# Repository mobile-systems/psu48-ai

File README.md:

# PSU48-800 — БП 220 В AC → 48 В DC, 800 Вт

Проект импульсного блока питания (PFC + LLC), разрабатывается в KiCad 10.

- `JOURNAL.md` — инженерный журнал (этапы, решения, изменения).
- `docs/SPEC.md` — техническое задание.
- `docs/DESIGN.md` — расчёт топологии.
- `kicad/` — проект KiCad (схема, плата, библиотеки).
- `tools/` — скрипты генерации и проверки (Python, bundled с KiCad).
- `production/` — производственные файлы (Gerber, drill, BOM, CPL, PDF).

Сборка проекта (генерация схемы/платы) и выпуск — см. журнал, этапы работ.

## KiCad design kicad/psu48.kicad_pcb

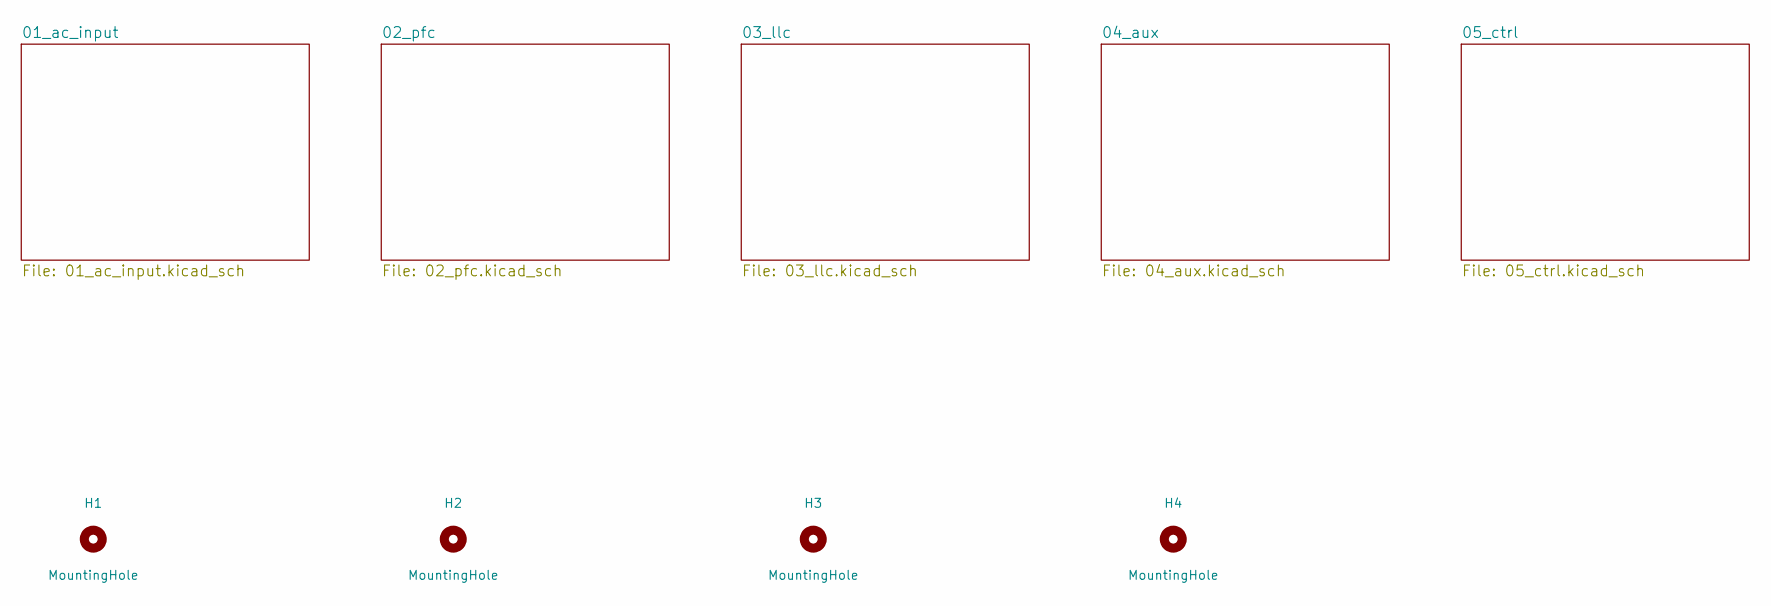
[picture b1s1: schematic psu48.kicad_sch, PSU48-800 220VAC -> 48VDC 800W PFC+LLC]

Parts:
H1, H2, H3, H4: MountingHole; MountingHole_3.2mm_M3

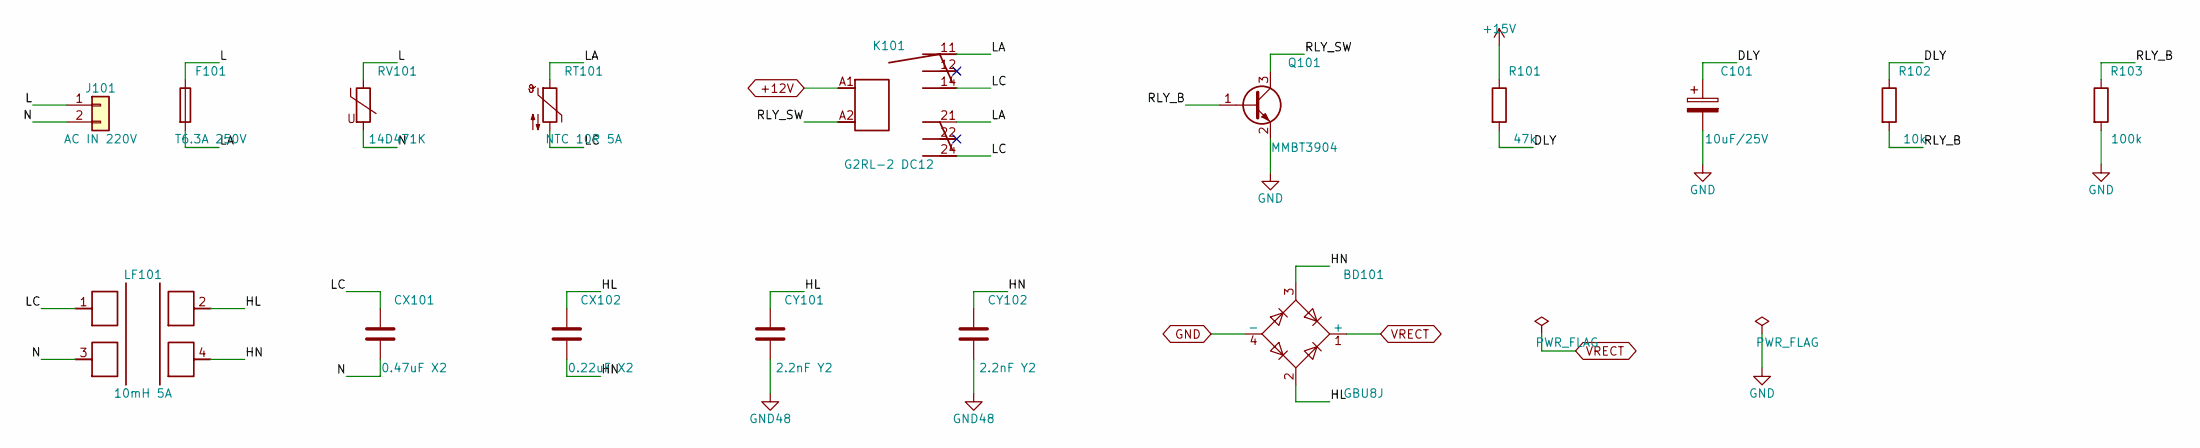
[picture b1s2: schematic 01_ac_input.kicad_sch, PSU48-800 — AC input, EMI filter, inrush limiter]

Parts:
BD101: GBU8J; Diode_Bridge_Vishay_GBU
C101: 10uF/25V; CP_Radial_D5.0mm_P2.50mm
CX101: 0.47uF X2; C_Rect_L27.0mm_W11.0mm_P22.00mm
CX102: 0.22uF X2; C_Rect_L16.5mm_W5.0mm_P15.00mm_MKT
CY101, CY102: 2.2nF Y2; C_Disc_D10.5mm_W5.0mm_P7.50mm
F101: T6.3A 250V; Fuseholder_Clip-5x20mm_Littelfuse_111_Inline_P20.00x5.00mm_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
J101: AC IN 220V; TerminalBlock_MaiXu_MX126-5.0-02P_1x02_P5.00mm
K101: G2RL-2 DC12; Relay_DPDT_Omron_G2RL-2
LF101: 10mH 5A; CMChoke_25x20_P20x10
Q101: MMBT3904; SOT-23
R101: 47k; R_0805_2012Metric
R102: 10k; R_0805_2012Metric
R103: 100k; R_0805_2012Metric
RT101: NTC 10R 5A; NTC_D11.0mm_P5.00mm
RV101: 14D471K; RV_Disc_D15.5mm_W5.9mm_P7.5mm

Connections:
01_ac_input/DLY: C101.1, R101.2, R102.1
01_ac_input/HL: BD101.2, CX102.1, CY101.1, LF101.2
01_ac_input/HN: BD101.3, CX102.2, CY102.1, LF101.4
01_ac_input/L: F101.1, J101.1, RV101.1
01_ac_input/LA: F101.2, K101.11, K101.21, RT101.1
01_ac_input/LC: CX101.1, K101.14, K101.24, LF101.1, RT101.2
01_ac_input/N: CX101.2, J101.2, LF101.3, RV101.2
01_ac_input/RLY_B: Q101.1 (B), R102.2, R103.1
01_ac_input/RLY_SW: K101.A2, Q101.3 (C)
+12V: K101.A1; also elsewhere on the board
+15V: R101.1; also elsewhere on the board
GND: BD101.4 (-), C101.2, Q101.2 (E), R103.2; also elsewhere on the board
GND48: CY101.2, CY102.2; also elsewhere on the board
VRECT: BD101.1 (+); also elsewhere on the board

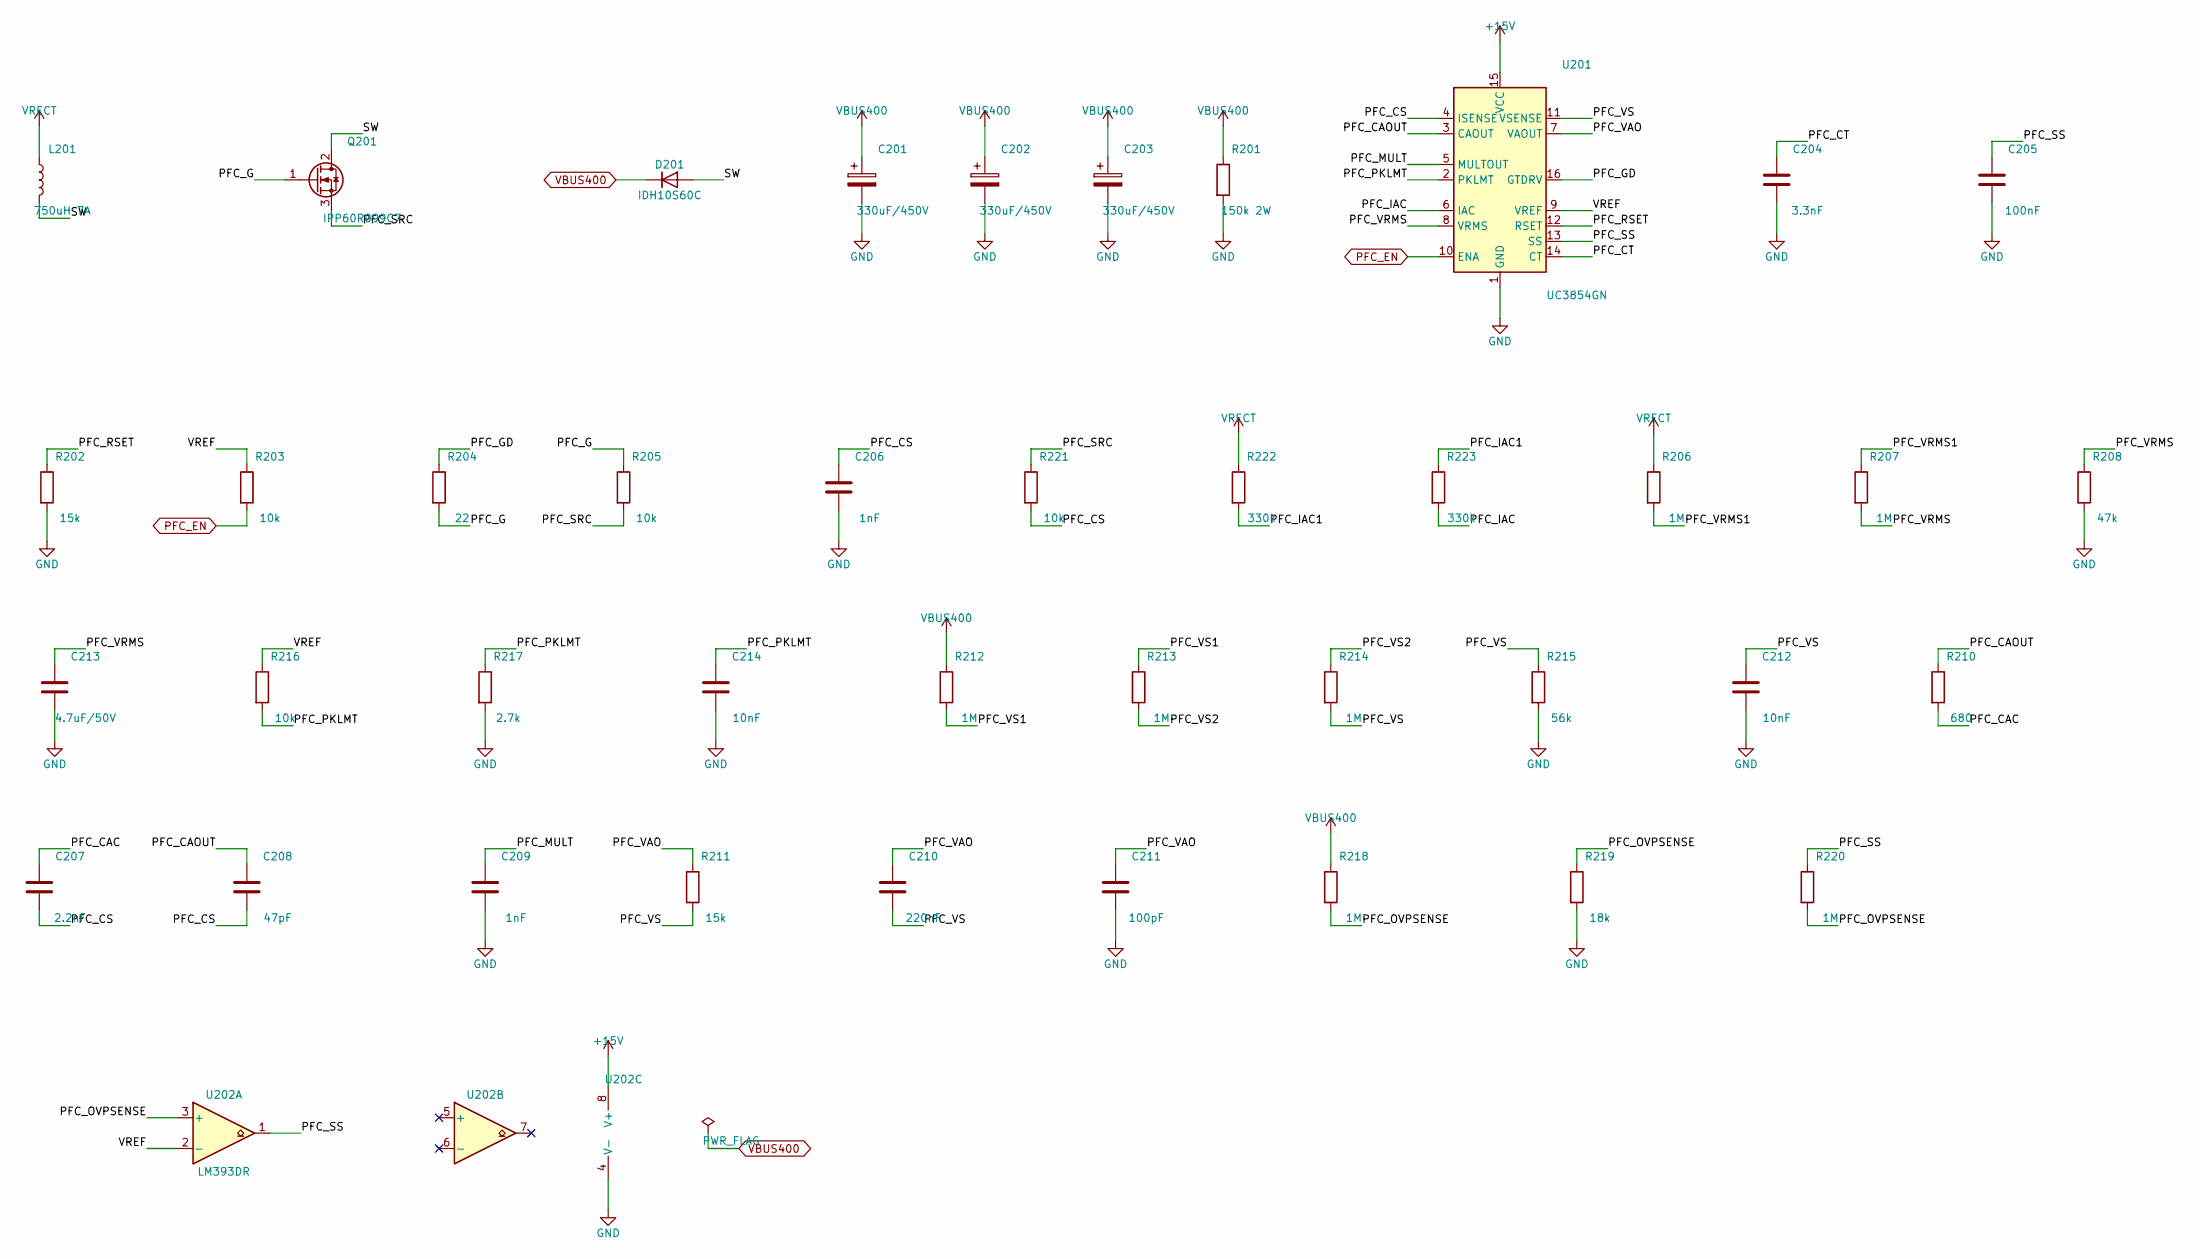
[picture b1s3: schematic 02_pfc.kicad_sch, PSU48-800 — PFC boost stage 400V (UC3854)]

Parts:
C201, C202, C203: 330uF/450V; CP_Radial_D35.0mm_P10.00mm
C204: 3.3nF; C_0805_2012Metric
C205: 100nF; C_0805_2012Metric
C206, C209: 1nF; C_0805_2012Metric
C207: 2.2nF; C_0805_2012Metric
C208: 47pF; C_0805_2012Metric
C210: 220nF; C_0805_2012Metric
C211: 100pF; C_0805_2012Metric
C212, C214: 10nF; C_0805_2012Metric
C213: 4.7uF/50V; C_1210_3225Metric
D201: IDH10S60C; TO-220-3_Vertical
L201: 750uH 7A; L_THT_D30.0mm_P15.00mm
Q201: IPP60R099C7; TO-220-3_Vertical
R201: 150k 2W; R_Axial_DIN0617_L17.0mm_D6.0mm_P25.40mm_Horizontal
R202, R211: 15k; R_0805_2012Metric
R203, R205, R216, R221: 10k; R_0805_2012Metric
R204: 22; R_0805_2012Metric
R206, R207, R212, R213, R214, R218: 1M; R_1206_3216Metric
R208: 47k; R_0805_2012Metric
R210: 680; R_0805_2012Metric
R215: 56k; R_0805_2012Metric
R217: 2.7k; R_0805_2012Metric
R219: 18k; R_0805_2012Metric
R220: 1M; R_0805_2012Metric
R222, R223: 330k; R_1206_3216Metric
U201: UC3854GN; DIP-16_W7.62mm
U202: LM393DR; SOIC-8_3.9x4.9mm_P1.27mm

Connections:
02_pfc/PFC_CAC: C207.1, R210.2
02_pfc/PFC_CAOUT: C208.1, R210.1, U201.3 (CAOUT)
02_pfc/PFC_CS: C206.1, C207.2, C208.2, R221.2, U201.4 (ISENSE)
02_pfc/PFC_CT: C204.1, U201.14 (CT)
02_pfc/PFC_G: Q201.1 (G), R204.2, R205.1
02_pfc/PFC_GD: R204.1, U201.16 (GTDRV)
02_pfc/PFC_IAC: R223.2, U201.6 (IAC)
02_pfc/PFC_IAC1: R222.2, R223.1
02_pfc/PFC_MULT: C209.1, U201.5 (MULTOUT)
02_pfc/PFC_OVPSENSE: R218.2, R219.1, R220.2, U202.3 (+)
02_pfc/PFC_PKLMT: C214.1, R216.2, R217.1, U201.2 (PKLMT)
02_pfc/PFC_RSET: R202.1, U201.12 (RSET)
02_pfc/PFC_SRC: Q201.3 (S), R205.2, R221.1
02_pfc/PFC_SS: C205.1, R220.1, U201.13 (SS), U202.1
02_pfc/PFC_VAO: C210.1, C211.1, R211.1, U201.7 (VAOUT)
02_pfc/PFC_VRMS: C213.1, R207.2, R208.1, U201.8 (VRMS)
02_pfc/PFC_VRMS1: R206.2, R207.1
02_pfc/PFC_VS: C210.2, C212.1, R211.2, R214.2, R215.1, U201.11 (VSENSE)
02_pfc/PFC_VS1: R212.2, R213.1
02_pfc/PFC_VS2: R213.2, R214.1
02_pfc/SW: D201.2 (A), L201.2, Q201.2 (D)
02_pfc/VREF: R203.1, R216.1, U201.9 (VREF), U202.2 (-)
+15V: U201.15 (VCC), U202.8 (V+); also elsewhere on the board
GND: C201.2, C202.2, C203.2, C204.2, C205.2, C206.2, C209.2, C211.2, C212.2, C213.2, C214.2, R201.2, R202.2, R208.2, R215.2, R217.2, R219.2, U201.1 (GND), U202.4 (V-); also elsewhere on the board
PFC_EN: R203.2, U201.10 (ENA); also elsewhere on the board
VBUS400: C201.1, C202.1, C203.1, D201.1 (K), R201.1, R212.1, R218.1; also elsewhere on the board
VRECT: L201.1, R206.1, R222.1; also elsewhere on the board

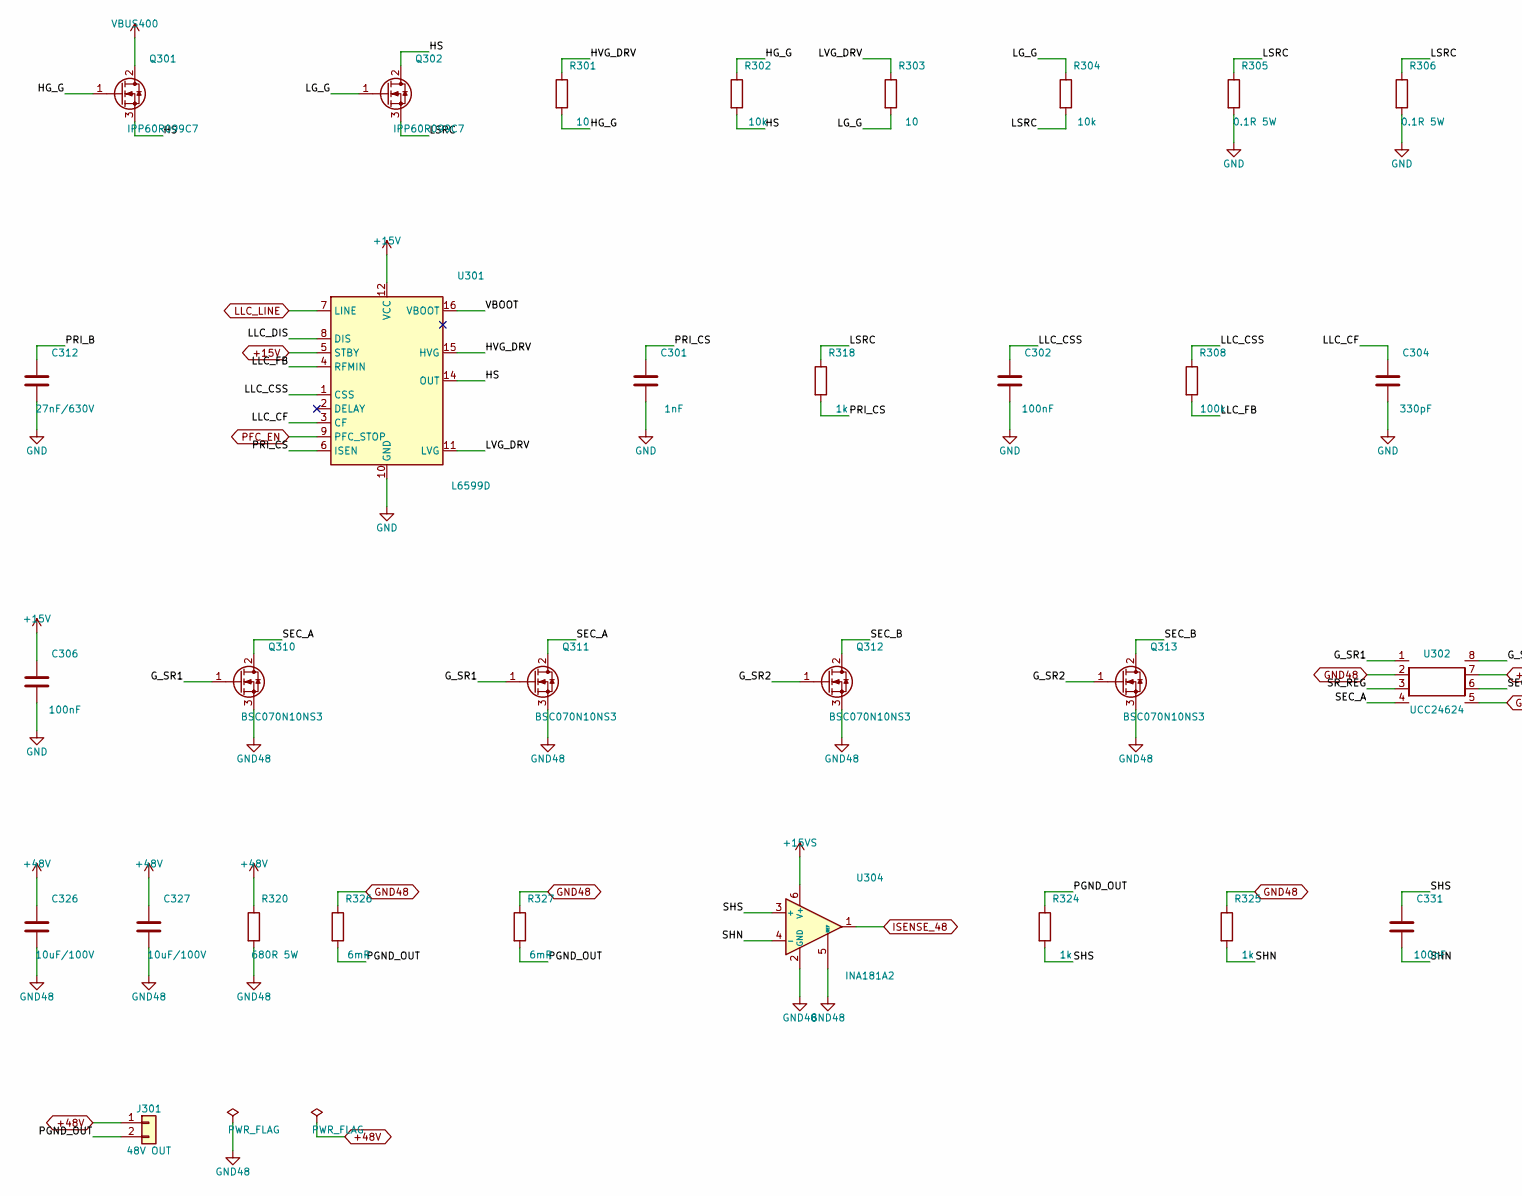
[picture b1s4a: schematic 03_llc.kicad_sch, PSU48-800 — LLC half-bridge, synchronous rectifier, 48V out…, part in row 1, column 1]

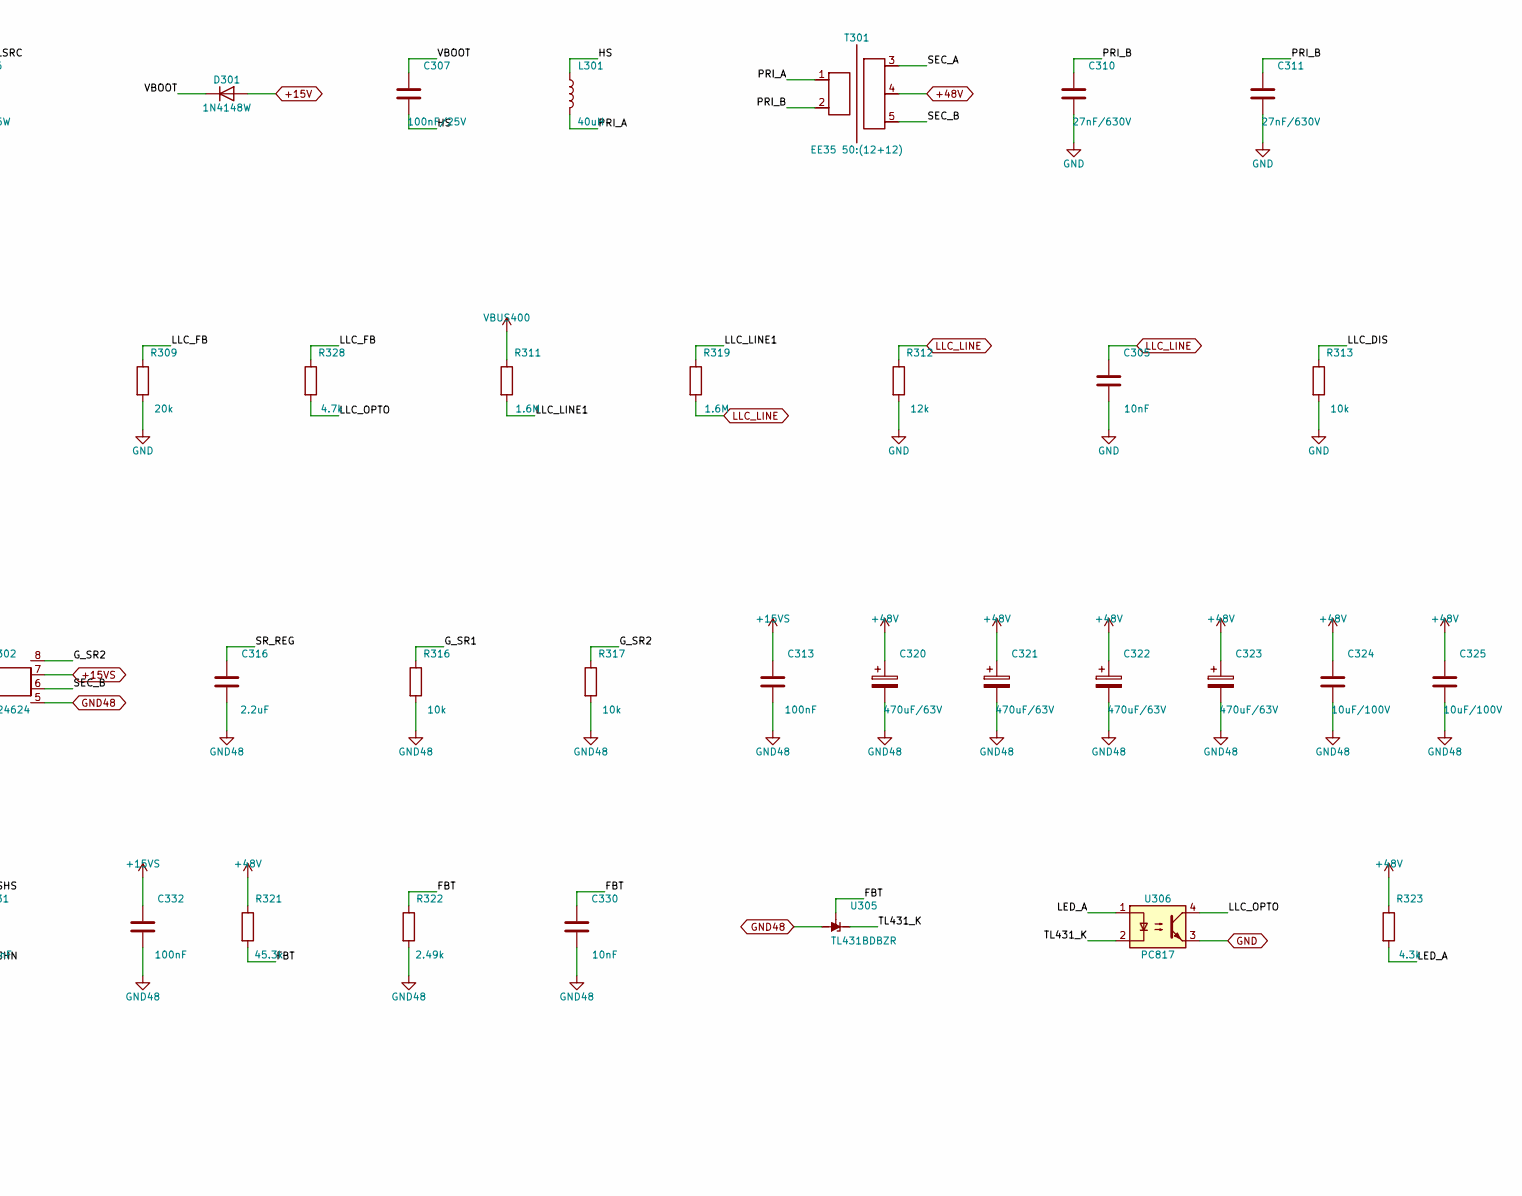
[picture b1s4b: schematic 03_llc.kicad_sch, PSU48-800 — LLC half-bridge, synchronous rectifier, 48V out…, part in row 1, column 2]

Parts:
C301: 1nF; C_0805_2012Metric
C302, C306, C313, C331, C332: 100nF; C_0805_2012Metric
C304: 330pF; C_0805_2012Metric
C305, C330: 10nF; C_0805_2012Metric
C307: 100nF/25V; C_0805_2012Metric
C310, C311, C312: 27nF/630V; C_Rect_L16.5mm_W5.0mm_P15.00mm_MKT
C316: 2.2uF; C_0805_2012Metric
C320, C321, C322, C323: 470uF/63V; CP_Radial_D16.0mm_P7.50mm
C324, C325, C326, C327: 10uF/100V; C_1210_3225Metric
D301: 1N4148W; D_SOD-123
J301: 48V OUT; PinHeader_1x02_P2.54mm_Vertical
L301: 40uH; L_THT_25x20_P10.00mm
Q301, Q302: IPP60R099C7; TO-247-3_Vertical
Q310, Q311, Q312, Q313: BSC070N10NS3; PQFN-8-EP_6x5mm_P1.27mm_Generic
R301, R303: 10; R_0805_2012Metric
R302, R304, R313, R316, R317: 10k; R_0805_2012Metric
R305, R306: 0.1R 5W; R_Axial_DIN0617_L17.0mm_D6.0mm_P25.40mm_Horizontal
R308: 100k; R_0805_2012Metric
R309: 20k; R_0805_2012Metric
R311, R319: 1.6M; R_1206_3216Metric
R312: 12k; R_0805_2012Metric
R318, R324, R325: 1k; R_0805_2012Metric
R320: 680R 5W; R_Axial_DIN0617_L17.0mm_D6.0mm_P25.40mm_Horizontal
R321: 45.3k; R_0805_2012Metric
R322: 2.49k; R_0805_2012Metric
R323: 4.3k; R_0805_2012Metric
R326, R327: 6mR; R_2512_6332Metric
R328: 4.7k; R_0805_2012Metric
T301: EE35 50:(12+12); T_EE35_5pin_P5.00mm
U301: L6599D; SOIC-16_3.9x9.9mm_P1.27mm
U302: UCC24624; SOIC-8_3.9x4.9mm_P1.27mm
U304: INA181A2; SOT-23-5
U305: TL431BDBZR; SOT-23-5
U306: PC817; DIP-4_W7.62mm

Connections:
03_llc/FBT: C330.1, R321.2, R322.1, U305.4 (REF)
03_llc/G_SR1: Q310.1 (G), Q311.1 (G), R316.1, U302.1 (VG1)
03_llc/G_SR2: Q312.1 (G), Q313.1 (G), R317.1, U302.8 (VG2)
03_llc/HG_G: Q301.1 (G), R301.2, R302.1
03_llc/HS: C307.2, L301.1, Q301.3 (S), Q302.2 (D), R302.2, U301.14 (OUT)
03_llc/HVG_DRV: R301.1, U301.15 (HVG)
03_llc/LED_A: R323.2, U306.1
03_llc/LG_G: Q302.1 (G), R303.2, R304.1
03_llc/LLC_CF: C304.1, U301.3 (CF)
03_llc/LLC_CSS: C302.1, R308.1, U301.1 (CSS)
03_llc/LLC_DIS: R313.1, U301.8 (DIS)
03_llc/LLC_FB: R308.2, R309.1, R328.1, U301.4 (RFMIN)
03_llc/LLC_LINE1: R311.2, R319.1
03_llc/LLC_OPTO: R328.2, U306.4
03_llc/LSRC: Q302.3 (S), R304.2, R305.1, R306.1, R318.1
03_llc/LVG_DRV: R303.1, U301.11 (LVG)
03_llc/PGND_OUT: J301.2, R324.1, R326.2, R327.2
03_llc/PRI_A: L301.2, T301.1
03_llc/PRI_B: C310.1, C311.1, C312.1, T301.2
03_llc/PRI_CS: C301.1, R318.2, U301.6 (ISEN)
03_llc/SEC_A: Q310.2 (D), Q311.2 (D), T301.3, U302.4 (VD1)
03_llc/SEC_B: Q312.2 (D), Q313.2 (D), T301.5, U302.6 (VD2)
03_llc/SHN: C331.2, R325.2, U304.4 (-)
03_llc/SHS: C331.1, R324.2, U304.3 (+)
03_llc/SR_REG: C316.1, U302.3 (REG)
03_llc/TL431_K: U305.3 (K), U306.2
03_llc/VBOOT: C307.1, D301.1 (K), U301.16 (VBOOT)
+15V: C306.1, D301.2 (A), U301.5 (STBY), U301.12 (VCC); also elsewhere on the board
+15VS: C313.1, C332.1, U302.7 (VDD), U304.6 (V+); also elsewhere on the board
+48V: C320.1, C321.1, C322.1, C323.1, C324.1, C325.1, C326.1, C327.1, J301.1, R320.1, R321.1, R323.1, T301.4; also elsewhere on the board
GND: C301.2, C302.2, C304.2, C305.2, C306.2, C310.2, C311.2, C312.2, R305.2, R306.2, R309.2, R312.2, R313.2, U301.10 (GND), U306.3; also elsewhere on the board
GND48: C313.2, C316.2, C320.2, C321.2, C322.2, C323.2, C324.2, C325.2, C326.2, C327.2, C330.2, C332.2, Q310.3 (S), Q311.3 (S), Q312.3 (S), Q313.3 (S), R316.2, R317.2, R320.2, R322.2, R325.1, R326.1, R327.1, U302.2 (PGND), U302.5 (VSS), U304.2 (GND), U304.5 (REF), U305.5 (A); also elsewhere on the board
ISENSE_48: U304.1; also elsewhere on the board
LLC_LINE: C305.1, R312.1, R319.2, U301.7 (LINE); also elsewhere on the board
PFC_EN: U301.9 (PFC_STOP); also elsewhere on the board
VBUS400: Q301.2 (D), R311.1; also elsewhere on the board

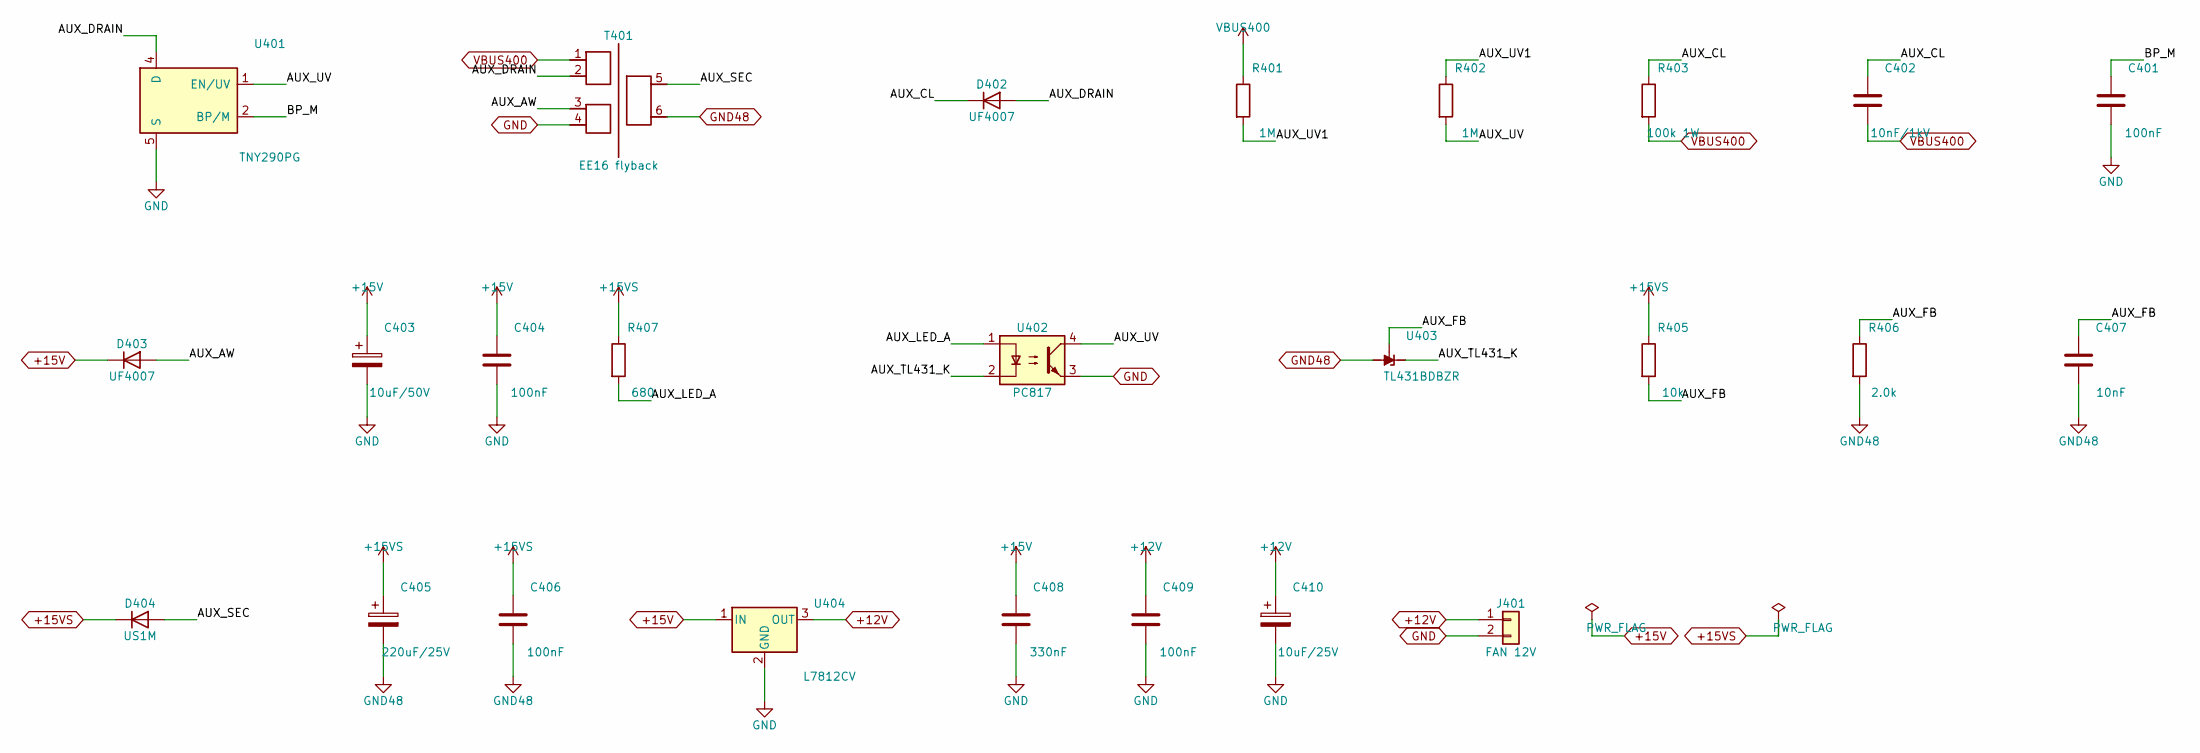
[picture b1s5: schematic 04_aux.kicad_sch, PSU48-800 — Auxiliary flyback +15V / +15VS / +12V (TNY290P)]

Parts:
C401, C404, C406, C409: 100nF; C_0805_2012Metric
C402: 10nF/1kV; C_Rect_L24.0mm_W10.1mm_P22.50mm_MKT
C403: 10uF/50V; CP_Radial_D5.0mm_P2.50mm
C405: 220uF/25V; CP_Radial_D10.0mm_P5.00mm
C407: 10nF; C_0805_2012Metric
C408: 330nF; C_0805_2012Metric
C410: 10uF/25V; CP_Radial_D5.0mm_P2.50mm
D402, D403: UF4007; D_DO-41_SOD81_P10.16mm_Horizontal
D404: US1M; D_SMA
J401: FAN 12V; PinHeader_1x02_P2.54mm_Vertical
R401, R402: 1M; R_1206_3216Metric
R403: 100k 1W; R_Axial_DIN0617_L17.0mm_D6.0mm_P25.40mm_Horizontal
R405: 10k; R_0805_2012Metric
R406: 2.0k; R_0805_2012Metric
R407: 680; R_0805_2012Metric
T401: EE16 flyback; T_EE16_6pin_P2.50mm
U401: TNY290PG; DIP-8_W7.62mm
U402: PC817; DIP-4_W7.62mm
U403: TL431BDBZR; SOT-23-5
U404: L7812CV; TO-220-3_Vertical

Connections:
04_aux/AUX_AW: D403.2 (A), T401.3
04_aux/AUX_CL: C402.1, D402.1 (K), R403.1
04_aux/AUX_DRAIN: D402.2 (A), T401.2, U401.4 (D)
04_aux/AUX_FB: C407.1, R405.2, R406.1, U403.4 (REF)
04_aux/AUX_LED_A: R407.2, U402.1
04_aux/AUX_SEC: D404.2 (A), T401.5
04_aux/AUX_TL431_K: U402.2, U403.3 (K)
04_aux/AUX_UV: R402.2, U401.1 (EN/UV), U402.4
04_aux/AUX_UV1: R401.2, R402.1
04_aux/BP_M: C401.1, U401.2 (BP/M)
+12V: C409.1, C410.1, J401.1, U404.3 (OUT); also elsewhere on the board
+15V: C403.1, C404.1, C408.1, D403.1 (K), U404.1 (IN); also elsewhere on the board
+15VS: C405.1, C406.1, D404.1 (K), R405.1, R407.1; also elsewhere on the board
GND: C401.2, C403.2, C404.2, C408.2, C409.2, C410.2, J401.2, T401.4, U401.5 (S), U401.6 (S), U401.7 (S), U401.8 (S), U402.3, U404.2 (GND); also elsewhere on the board
GND48: C405.2, C406.2, C407.2, R406.2, T401.6, U403.5 (A); also elsewhere on the board
VBUS400: C402.2, R401.1, R403.2, T401.1; also elsewhere on the board

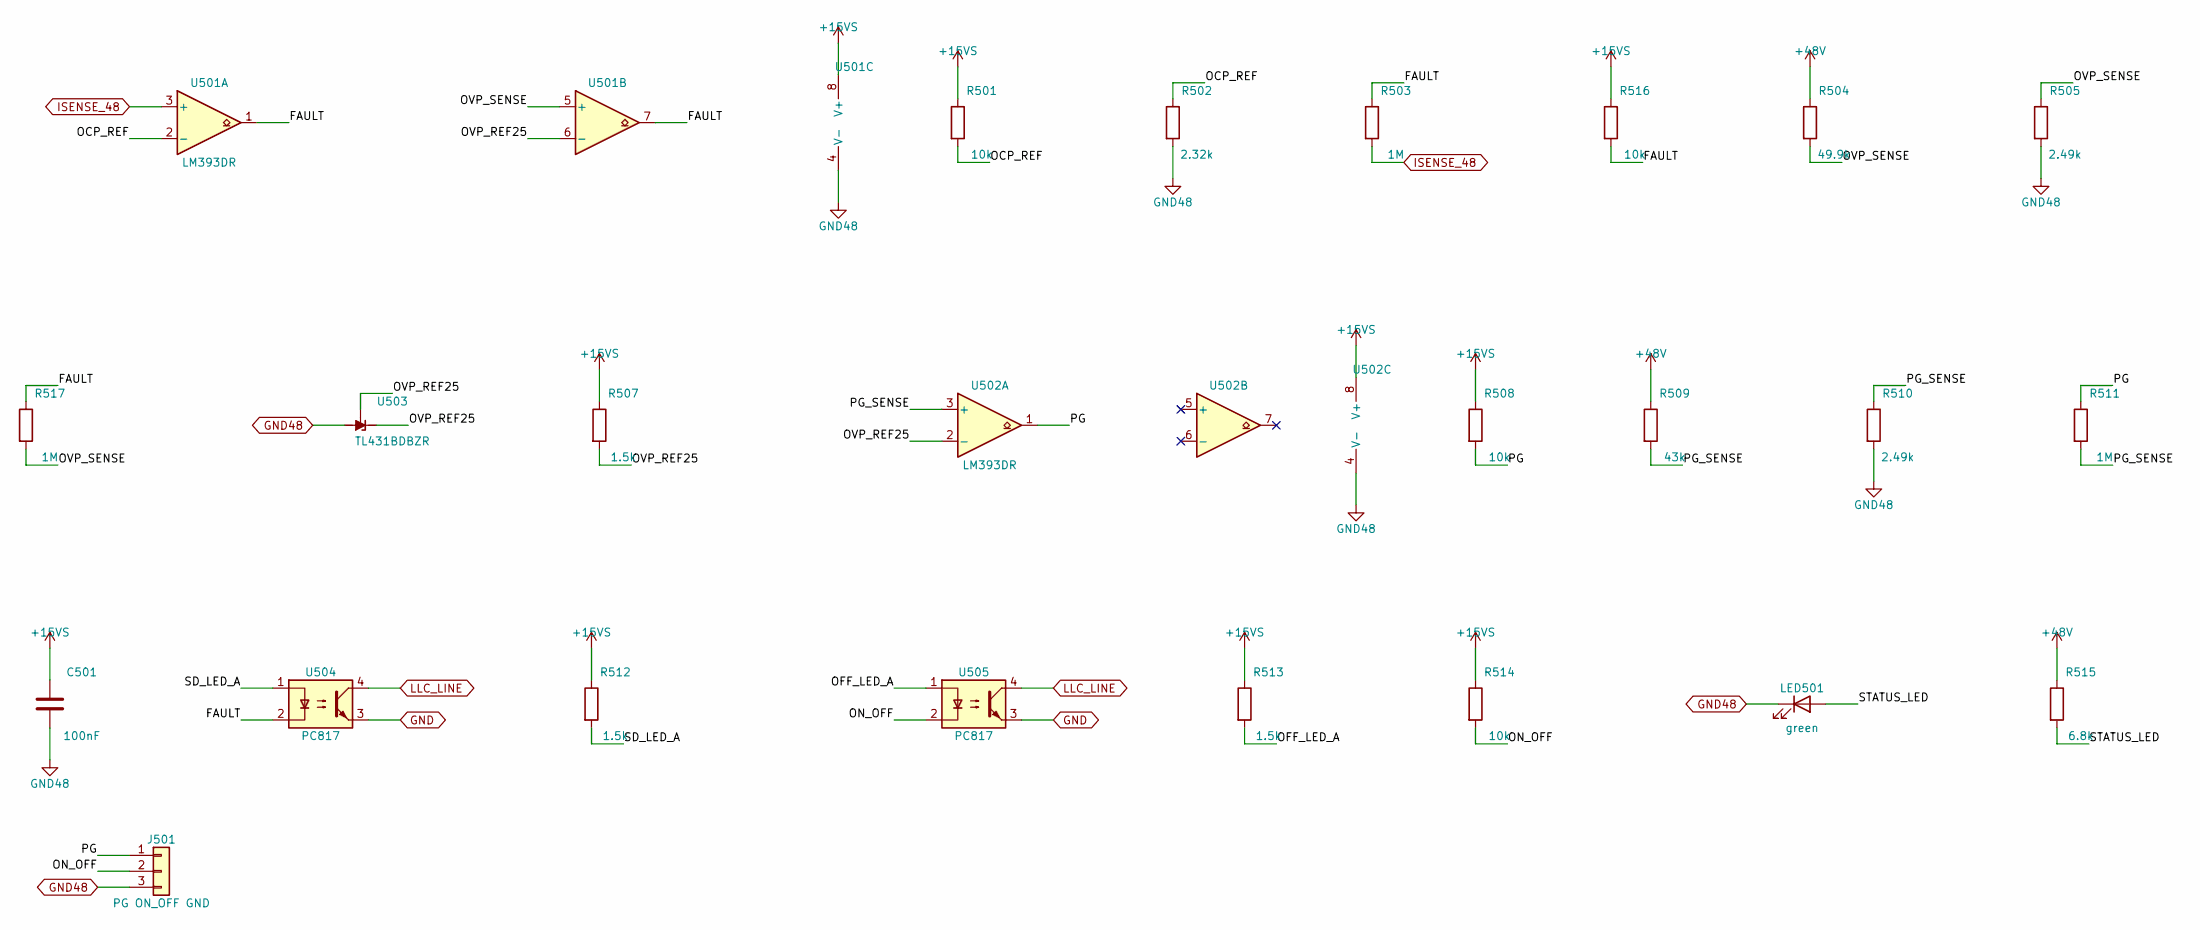
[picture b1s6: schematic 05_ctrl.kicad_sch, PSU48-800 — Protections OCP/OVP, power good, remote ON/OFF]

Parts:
C501: 100nF; C_0805_2012Metric
J501: PG ON_OFF GND; PinHeader_1x03_P2.54mm_Vertical
LED501: green; LED_0805_2012Metric
R501, R508, R514, R516: 10k; R_0805_2012Metric
R502: 2.32k; R_0805_2012Metric
R503, R511, R517: 1M; R_0805_2012Metric
R504: 49.9k; R_1206_3216Metric
R505, R510: 2.49k; R_0805_2012Metric
R507, R512, R513: 1.5k; R_0805_2012Metric
R509: 43k; R_1206_3216Metric
R515: 6.8k; R_0805_2012Metric
U501, U502: LM393DR; SOIC-8_3.9x4.9mm_P1.27mm
U503: TL431BDBZR; SOT-23-5
U504, U505: PC817; DIP-4_W7.62mm

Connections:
05_ctrl/FAULT: R503.1, R516.2, R517.1, U501.1, U501.7, U504.2
05_ctrl/OCP_REF: R501.2, R502.1, U501.2 (-)
05_ctrl/OFF_LED_A: R513.2, U505.1
05_ctrl/ON_OFF: J501.2, R514.2, U505.2
05_ctrl/OVP_REF25: R507.2, U501.6 (-), U502.2 (-), U503.3 (K), U503.4 (REF)
05_ctrl/OVP_SENSE: R504.2, R505.1, R517.2, U501.5 (+)
05_ctrl/PG: J501.1, R508.2, R511.1, U502.1
05_ctrl/PG_SENSE: R509.2, R510.1, R511.2, U502.3 (+)
05_ctrl/SD_LED_A: R512.2, U504.1
05_ctrl/STATUS_LED: LED501.2 (A), R515.2
+15VS: C501.1, R501.1, R507.1, R508.1, R512.1, R513.1, R514.1, R516.1, U501.8 (V+), U502.8 (V+); also elsewhere on the board
+48V: R504.1, R509.1, R515.1; also elsewhere on the board
GND: U504.3, U505.3; also elsewhere on the board
GND48: C501.2, J501.3, LED501.1 (K), R502.2, R505.2, R510.2, U501.4 (V-), U502.4 (V-), U503.5 (A); also elsewhere on the board
ISENSE_48: R503.2, U501.3 (+); also elsewhere on the board
LLC_LINE: U504.4, U505.4; also elsewhere on the board

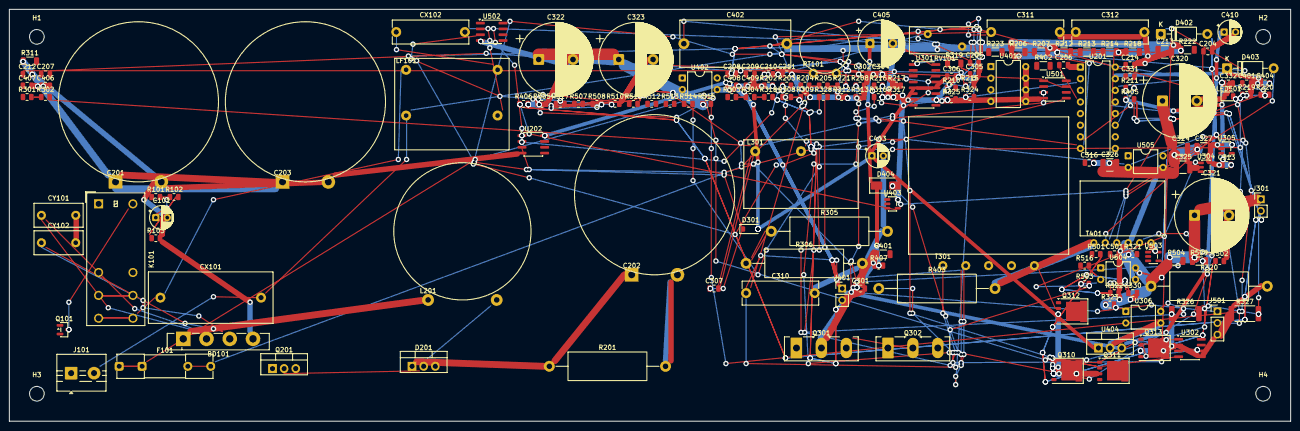
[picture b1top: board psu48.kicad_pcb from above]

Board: 2 copper layers, 280.0 x 90.0 mm, 171 parts (0 on the bottom side), 89 nets.
